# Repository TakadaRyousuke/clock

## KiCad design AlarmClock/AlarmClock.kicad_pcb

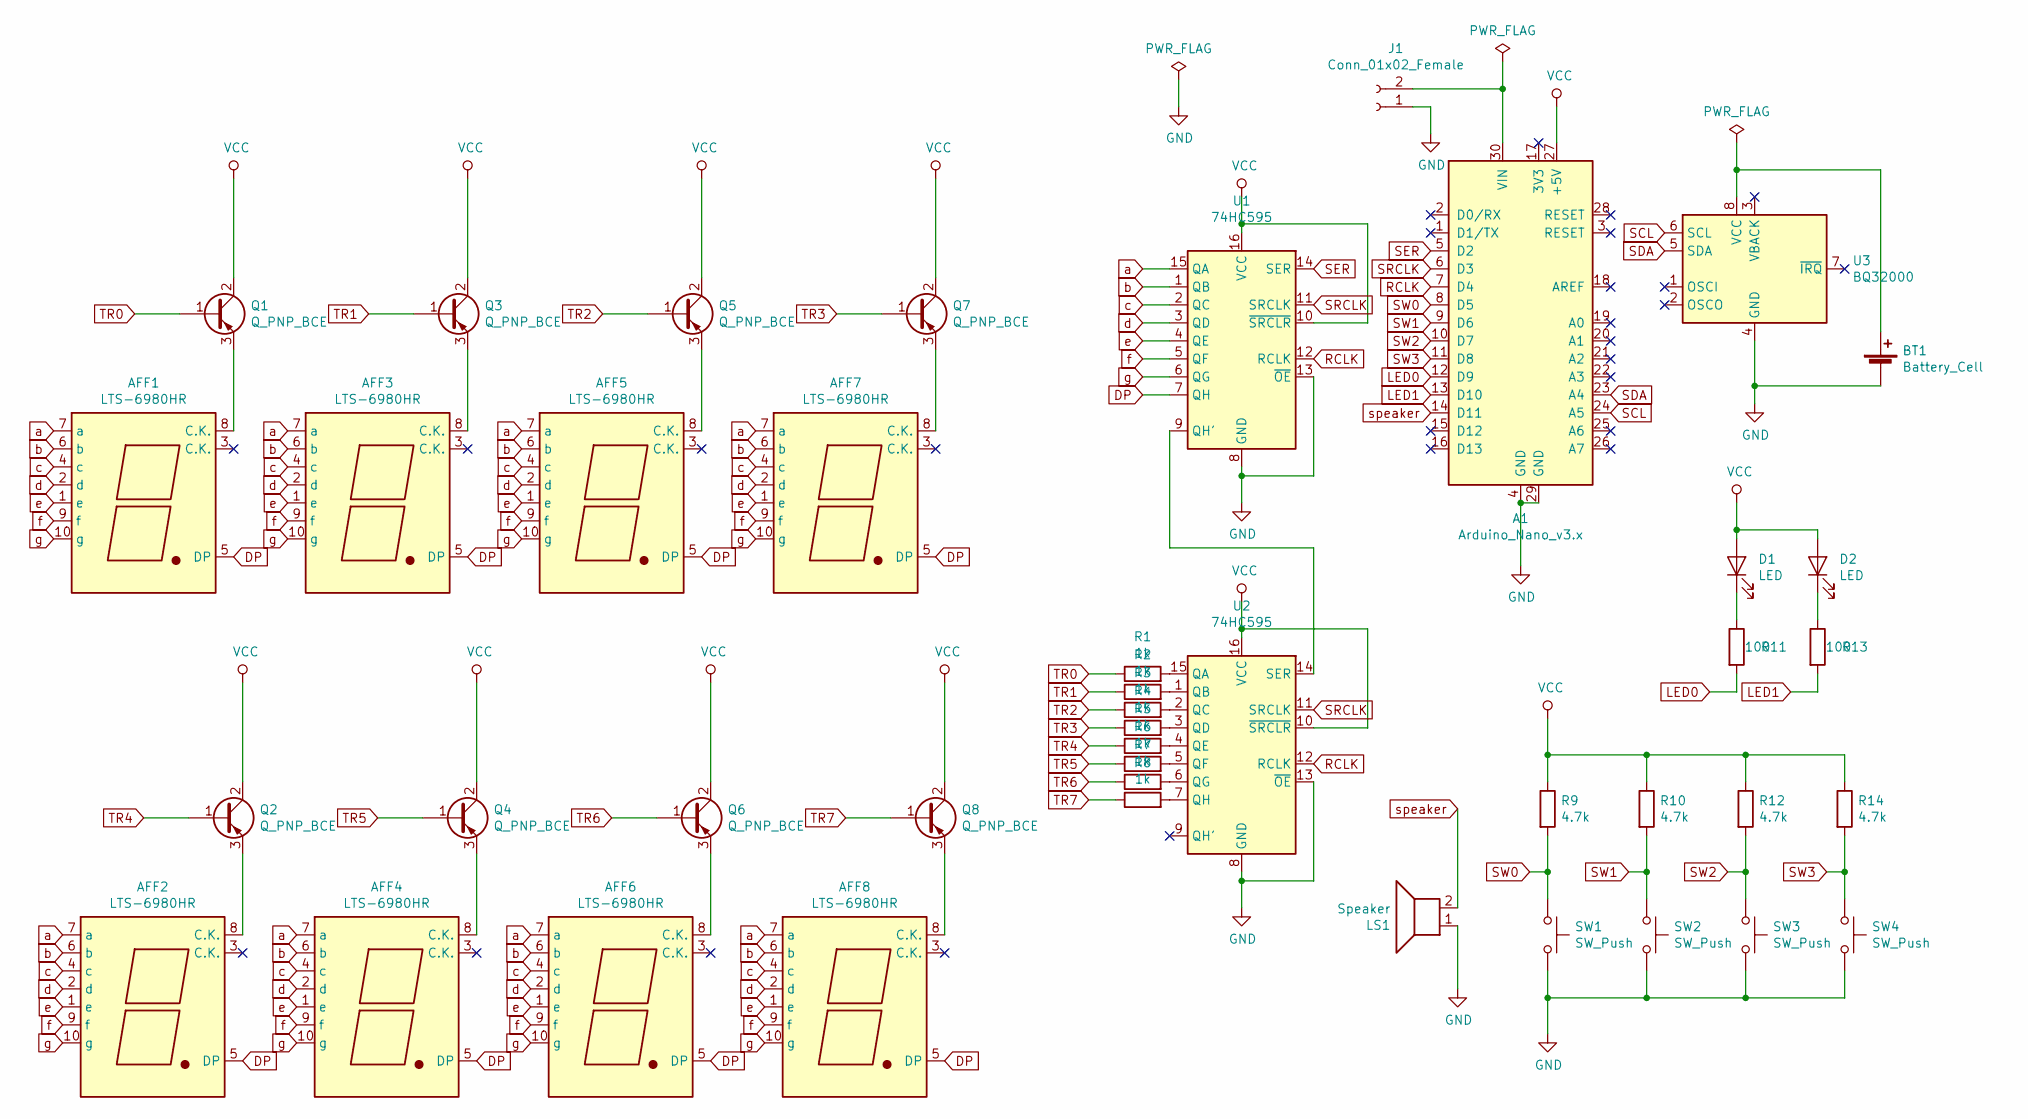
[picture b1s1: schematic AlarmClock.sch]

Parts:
A1: Arduino_Nano_v3.x; Arduino_Nano
AFF1, AFF2, AFF3, AFF4, AFF5, AFF6, AFF7, AFF8: LTS-6980HR; 7SegmentLED_LTS6760_LTS6780
BT1: Battery_Cell; BatteryHolder_Keystone_104_1x23mm
D1, D2: LED; LED_D5.0mm
J1: Conn_01x02_Female; BarrelJack_Horizontal
LS1: Speaker; PinSocket_2x01_P2.54mm_Vertical
Q1, Q2, Q3, Q4, Q5, Q6, Q7, Q8: Q_PNP_BCE; TO-92L
R1, R2, R3, R4, R5, R6, R7, R8: 1k; R_Axial_DIN0309_L9.0mm_D3.2mm_P12.70mm_Horizontal
R9, R10, R12, R14: 4.7k; R_Axial_DIN0309_L9.0mm_D3.2mm_P12.70mm_Horizontal
R11, R13: 100; R_Axial_DIN0309_L9.0mm_D3.2mm_P12.70mm_Horizontal
SW1, SW2, SW3, SW4: SW_Push; SW_PUSH_6mm_H5mm
U1, U2: 74HC595; DIP-16_W7.62mm_LongPads
U3: BQ32000; DIP-8_W10.16mm_LongPads

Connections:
DP: AFF1.5 (DP), AFF2.5 (DP), AFF3.5 (DP), AFF4.5 (DP), AFF5.5 (DP), AFF6.5 (DP), AFF7.5 (DP), AFF8.5 (DP), U1.7 (QH)
GND: A1.4 (GND), A1.29 (GND), BT1.2 (-), J1.1, LS1.1, SW1.2, SW2.2, SW3.2, SW4.2, U1.8 (GND), U1.13 (~OE), U2.8 (GND), U2.13 (~OE), U3.4 (GND); also elsewhere on the board
LED0: A1.12 (D9), R11.2; also elsewhere on the board
LED1: A1.13 (D10), R13.2; also elsewhere on the board
unnamed: A1.23 (A4), U3.5 (SDA)
unnamed: A1.24 (A5), U3.6 (SCL)
unnamed 20: A1.30 (VIN), J1.2; also elsewhere on the board
unnamed: AFF1.8 (C.K.), Q1.3 (E)
unnamed: AFF2.8 (C.K.), Q2.3 (E)
unnamed: AFF3.8 (C.K.), Q3.3 (E)
unnamed: AFF4.8 (C.K.), Q4.3 (E)
unnamed: AFF5.8 (C.K.), Q5.3 (E)
unnamed: AFF6.8 (C.K.), Q6.3 (E)
unnamed: AFF7.8 (C.K.), Q7.3 (E)
unnamed: AFF8.8 (C.K.), Q8.3 (E)
unnamed 37: BT1.1 (+), U3.8 (VCC); also elsewhere on the board
unnamed: D1.1 (K), R11.1
unnamed: D2.1 (K), R13.1
unnamed: R1.2, U2.15 (QA)
unnamed: R2.2, U2.1 (QB)
unnamed: R3.2, U2.2 (QC)
unnamed: R4.2, U2.3 (QD)
unnamed: R5.2, U2.4 (QE)
unnamed: R6.2, U2.5 (QF)
unnamed: R7.2, U2.6 (QG)
unnamed: R8.2, U2.7 (QH)
unnamed: U1.9 (QH'), U2.14 (SER)
RCLK: A1.7 (D4), U1.12 (RCLK), U2.12 (RCLK); also elsewhere on the board
SER: A1.5 (D2), U1.14 (SER); also elsewhere on the board
SRCLK: A1.6 (D3), U1.11 (SRCLK), U2.11 (SRCLK); also elsewhere on the board
SW0: A1.8 (D5), R9.2, SW1.1; also elsewhere on the board
SW1: A1.9 (D6), R10.2, SW2.1; also elsewhere on the board
SW2: A1.10 (D7), R12.2, SW3.1; also elsewhere on the board
SW3: A1.11 (D8), R14.2, SW4.1; also elsewhere on the board
TR0: Q1.1 (B), R1.1
TR1: Q3.1 (B), R2.1
TR2: Q5.1 (B), R3.1
TR3: Q7.1 (B), R4.1
TR4: Q2.1 (B), R5.1
TR5: Q4.1 (B), R6.1
TR6: Q6.1 (B), R7.1
TR7: Q8.1 (B), R8.1
VCC: A1.27 (+5V), D1.2 (A), D2.2 (A), Q1.2 (C), Q2.2 (C), Q3.2 (C), Q4.2 (C), Q5.2 (C), Q6.2 (C), Q7.2 (C), Q8.2 (C), R9.1, R10.1, R12.1, R14.1, U1.10 (~SRCLR), U1.16 (VCC), U2.10 (~SRCLR), U2.16 (VCC); also elsewhere on the board
a: AFF1.7 (a), AFF2.7 (a), AFF3.7 (a), AFF4.7 (a), AFF5.7 (a), AFF6.7 (a), AFF7.7 (a), AFF8.7 (a), U1.15 (QA)
b: AFF1.6 (b), AFF2.6 (b), AFF3.6 (b), AFF4.6 (b), AFF5.6 (b), AFF6.6 (b), AFF7.6 (b), AFF8.6 (b), U1.1 (QB)
c: AFF1.4 (c), AFF2.4 (c), AFF3.4 (c), AFF4.4 (c), AFF5.4 (c), AFF6.4 (c), AFF7.4 (c), AFF8.4 (c), U1.2 (QC)
d: AFF1.2 (d), AFF2.2 (d), AFF3.2 (d), AFF4.2 (d), AFF5.2 (d), AFF6.2 (d), AFF7.2 (d), AFF8.2 (d), U1.3 (QD)
e: AFF1.1 (e), AFF2.1 (e), AFF3.1 (e), AFF4.1 (e), AFF5.1 (e), AFF6.1 (e), AFF7.1 (e), AFF8.1 (e), U1.4 (QE)
f: AFF1.9 (f), AFF2.9 (f), AFF3.9 (f), AFF4.9 (f), AFF5.9 (f), AFF6.9 (f), AFF7.9 (f), AFF8.9 (f), U1.5 (QF)
g: AFF1.10 (g), AFF2.10 (g), AFF3.10 (g), AFF4.10 (g), AFF5.10 (g), AFF6.10 (g), AFF7.10 (g), AFF8.10 (g), U1.6 (QG)
speaker: A1.14 (D11), LS1.2; also elsewhere on the board

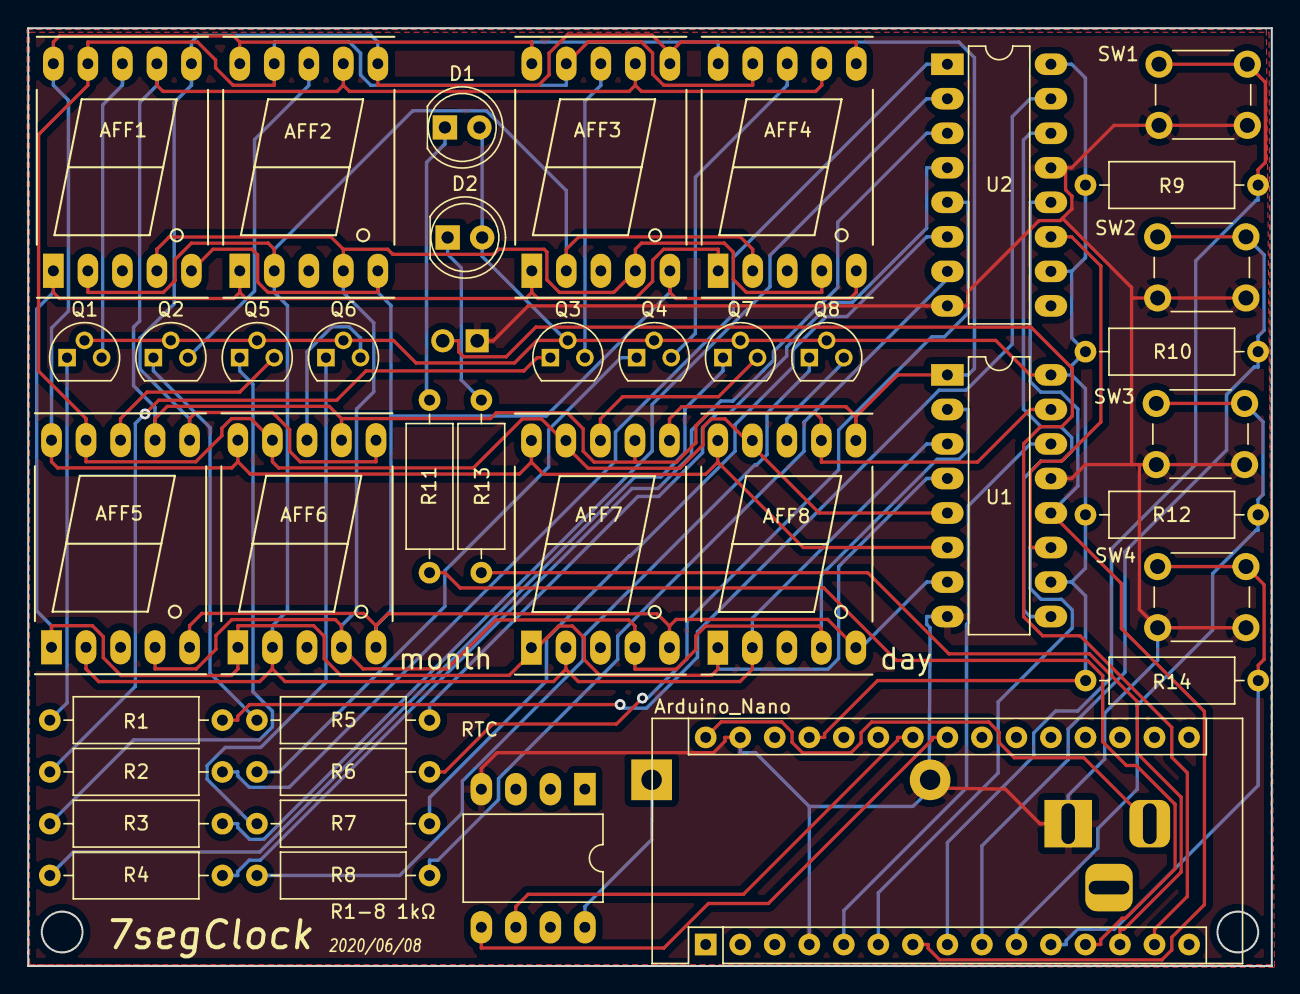
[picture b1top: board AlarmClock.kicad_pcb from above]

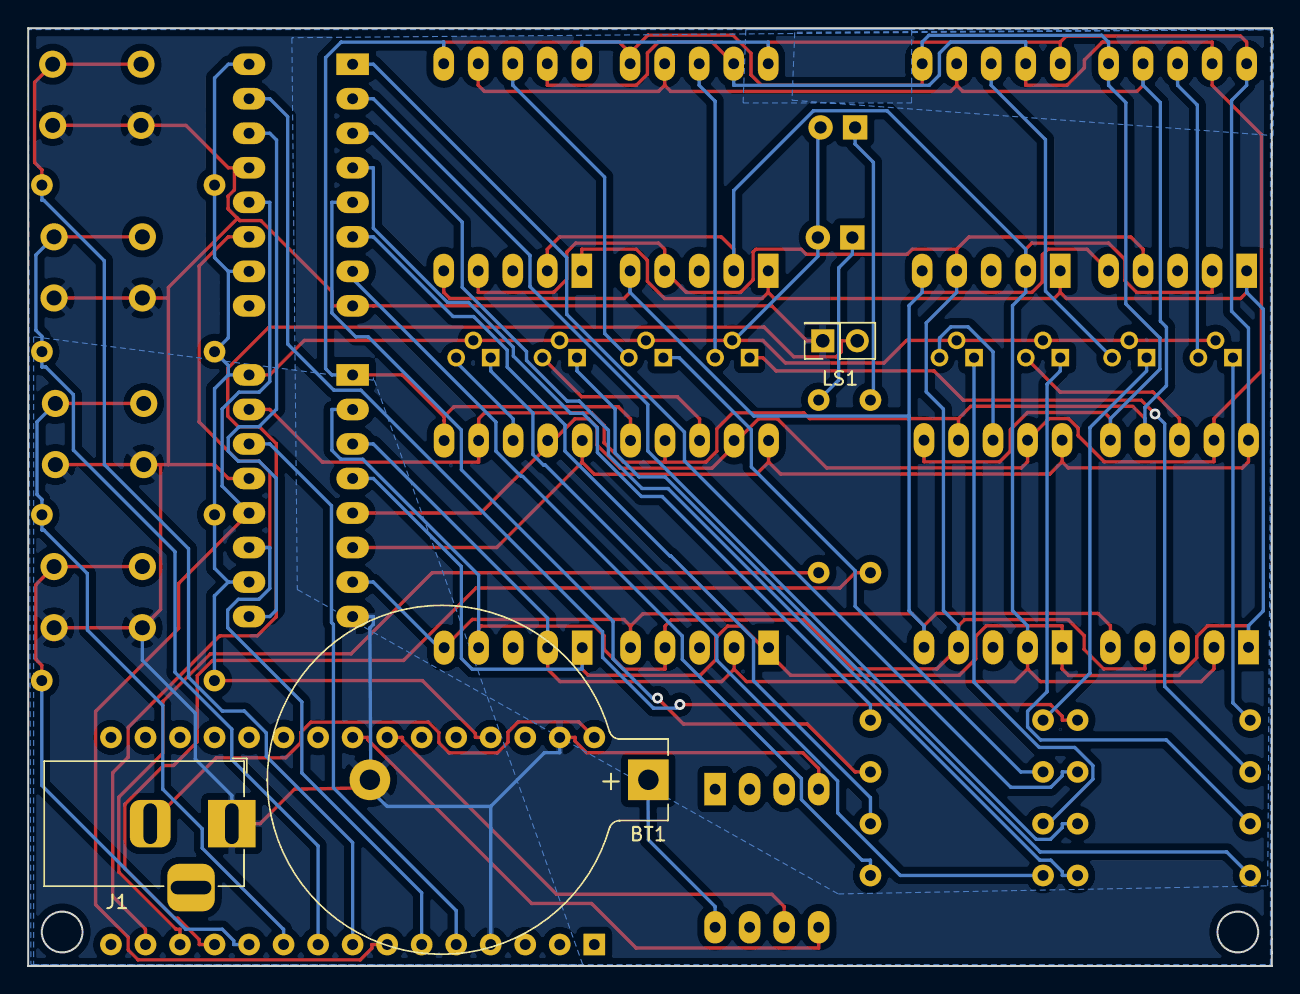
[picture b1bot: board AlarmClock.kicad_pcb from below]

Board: 2 copper layers, 91.5 x 69.0 mm, 43 parts (3 on the bottom side), 51 nets.

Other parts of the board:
Arduino_Nano: Arduino_Nano_v3.x; Arduino_Nano
RTC: BQ32000; DIP-8_W10.16mm_LongPads

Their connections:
GND: Arduino_Nano.4, Arduino_Nano.29, RTC.4; also elsewhere on the board
LED0: Arduino_Nano.12; also elsewhere on the board
LED1: Arduino_Nano.13; also elsewhere on the board
unnamed 20: Arduino_Nano.30; also elsewhere on the board
unnamed 37: RTC.8; also elsewhere on the board
RCLK: Arduino_Nano.7; also elsewhere on the board
SCL: Arduino_Nano.24, RTC.6
SDA: Arduino_Nano.23, RTC.5
SER: Arduino_Nano.5; also elsewhere on the board
SRCLK: Arduino_Nano.6; also elsewhere on the board
SW0: Arduino_Nano.8; also elsewhere on the board
SW1: Arduino_Nano.9; also elsewhere on the board
SW2: Arduino_Nano.10; also elsewhere on the board
SW3: Arduino_Nano.11; also elsewhere on the board
VCC: Arduino_Nano.27; also elsewhere on the board
speaker: Arduino_Nano.14; also elsewhere on the board
